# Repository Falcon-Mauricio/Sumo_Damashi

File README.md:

# Sumo DAMASHI

**Damashi** es un robot de sumo autónomo diseñado para competir en la disciplina de **<a href="https://lnr-argentina.com.ar/reglamentos/Reglamento%20Sumo.pdf" target="_blank">Sumo autónomo</a>** organizada por la **<a href="https://lnr-argentina.com.ar/" target="_blank">LNR</a>**.  

<div align="center">
  
</div>

---

## 🚀 Características principales

| Especificación | Detalle |
|----------------|---------|
| **Dimensiones** | 190x190x65 mm |
| **Peso** | ≤ 2500 g |
| **Chasis** | Impreso en 3D |
| **Batería** | LiPo 4S |
| **Microcontrolador** | ESP32 DevKit V1 |
| **Sensores** | 3 x QRE1113GR (tatami) + 5 x SHARP GP2Y0A02YK0F de distancia (laterales y frontales) |
| **Motores** | APYS SP6 - 260 RPM |
| **Driver de motores** | BTS7960 |

---

## ⚡ Entradas / Salidas (I/O)

<table>
<tr>

<td>

### Entradas (sensores y botones)

| Pin ESP32 | Descripción |
|-----------|-------------|
| GPIO34 | SHARP_LEFT |
| GPIO35 | SHARP_RIGHT |
| GPIO32 | SHARP_MID_LEFT |
| GPIO33 | SHARP_MID |
| GPIO25 | SHARP_MID_RIGHT |
| GPIO26 | TATAMI_B (sensor tatami trasero) |
| GPIO27 | TATAMI_L (sensor tatami izquierdo) |
| GPIO13 | TATAMI_R (sensor tatami derecho) |
| GPIO17 | PUSH_2 |
| GPIO18 | PUSH_1 |

</td>

<td>

### Salidas (motores y otros)

| Pin ESP32 | Descripción |
|-----------|-------------|
| GPIO23 | M2B |
| GPIO22 | M2A |
| GPIO19 | M1A |
| GPIO21 | M1B |
| GPIO18 | BUZZER |
| GPIO05 | LED_1 |

</td>

</tr>
</table>

---

## 🛠 Tecnologías utilizadas

- **FreeCAD** → Diseño de piezas 3D (soporte de motores, chasis y demas piezas auxiliares)  
- **KiCad** → Diseño del PCB  
- **PlatformIO (VSCode)** → Firmware en ESP32 (C++ / Arduino framework)  

---

## 📂 Archivos

- `1_hardware_pcb/` → Archivos de KiCad (PCB + esquemas)  
- `2_hardware_chasis/` → Archivos Free

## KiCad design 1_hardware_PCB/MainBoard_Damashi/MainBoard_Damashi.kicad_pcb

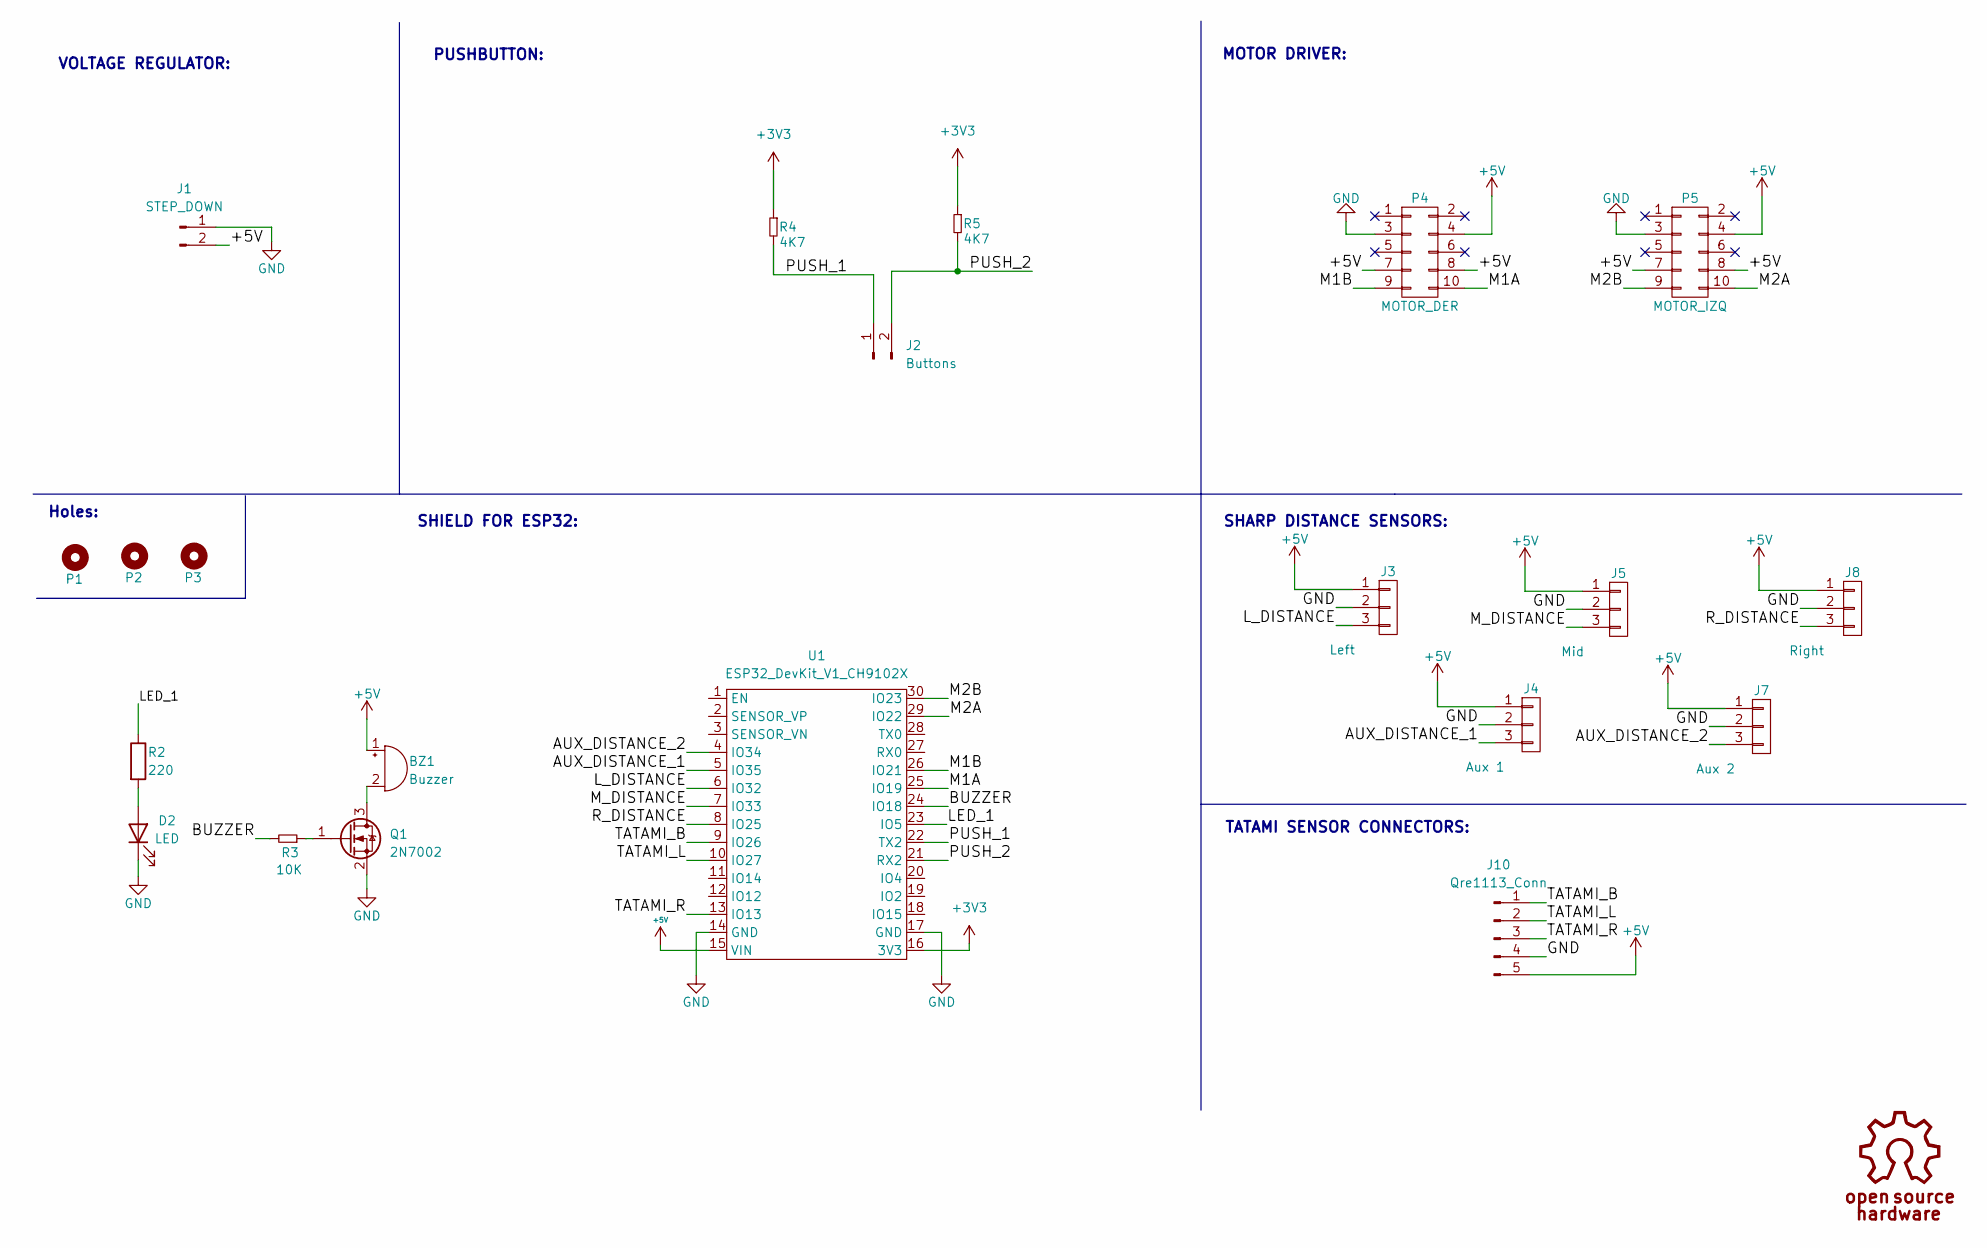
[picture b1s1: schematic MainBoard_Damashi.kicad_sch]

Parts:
BZ1: Buzzer; Buzzer_12mm
D2: LED; PinHeader_1x02_P2.54mm_Horizontal
J1: STEP_DOWN; PinHeader_1x02_P2.54mm_Horizontal
J2: Buttons; PinHeader_1x02_P2.54mm_Horizontal
J3: Left; FanPinHeader_1x03_P2.54mm_Vertical
J4: Aux 1; FanPinHeader_1x03_P2.54mm_Vertical
J5: Mid; FanPinHeader_1x03_P2.54mm_Vertical
J7: Aux 2; FanPinHeader_1x03_P2.54mm_Vertical
J8: Right; FanPinHeader_1x03_P2.54mm_Vertical
J10: Qre1113_Conn; PinHeader_1x05_P2.54mm_Horizontal
P1, P2, P3: Mounting_Hole; Separador_M3_5mm
P4: MOTOR_DER; Header_2x05x2.54mm_Vertical
P5: MOTOR_IZQ; Header_2x05x2.54mm_Vertical
Q1: 2N7002; SOT-23
R2: 220; R_1206
R3: 10K; R_1206
R4, R5: 4K7; R_1206
U1: ESP32_DevKit_V1_CH9102X

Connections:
+3V3: R4.1, R5.1, U1.16 (3V3)
+5V: BZ1.1 (-), J1.2, J3.1, J4.1, J5.1, J7.1, J8.1, J10.5, P4.4, P4.7, P4.8, P5.4, P5.7, P5.8, U1.15 (VIN)
/AUX_DISTANCE_1: J4.3, U1.5 (IO35)
/AUX_DISTANCE_2: J7.3, U1.4 (IO34)
/BUZZER: R3.2, U1.24 (IO18)
/LED_1: R2.1, U1.23 (IO5)
/L_DISTANCE: J3.3, U1.6 (IO32)
/M1A: P4.10, U1.25 (IO19)
/M1B: P4.9, U1.26 (IO21)
/M2A: P5.10, U1.29 (IO22)
/M2B: P5.9, U1.30 (IO23)
/M_DISTANCE: J5.3, U1.7 (IO33)
/PUSH_1: J2.1, R4.2, U1.22 (TX2)
/PUSH_2: J2.2, R5.2, U1.21 (RX2)
/R_DISTANCE: J8.3, U1.8 (IO25)
/TATAMI_B: J10.1, U1.9 (IO26)
/TATAMI_L: J10.2, U1.10 (IO27)
/TATAMI_R: J10.3, U1.13 (IO13)
GND: D2.1 (K), J1.1, J3.2, J4.2, J5.2, J7.2, J8.2, J10.4, P4.3, P5.3, Q1.2 (S), U1.14 (GND), U1.17 (GND)
unnamed: BZ1.2 (+), Q1.3 (D)
unnamed: D2.2 (A), R2.2
unnamed: Q1.1 (G), R3.1

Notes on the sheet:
TATAMI SENSOR CONNECTORS:
SHARP DISTANCE SENSORS:
MOTOR DRIVER:
VOLTAGE REGULATOR:
Holes:
PUSHBUTTON:
SHIELD FOR ESP32:

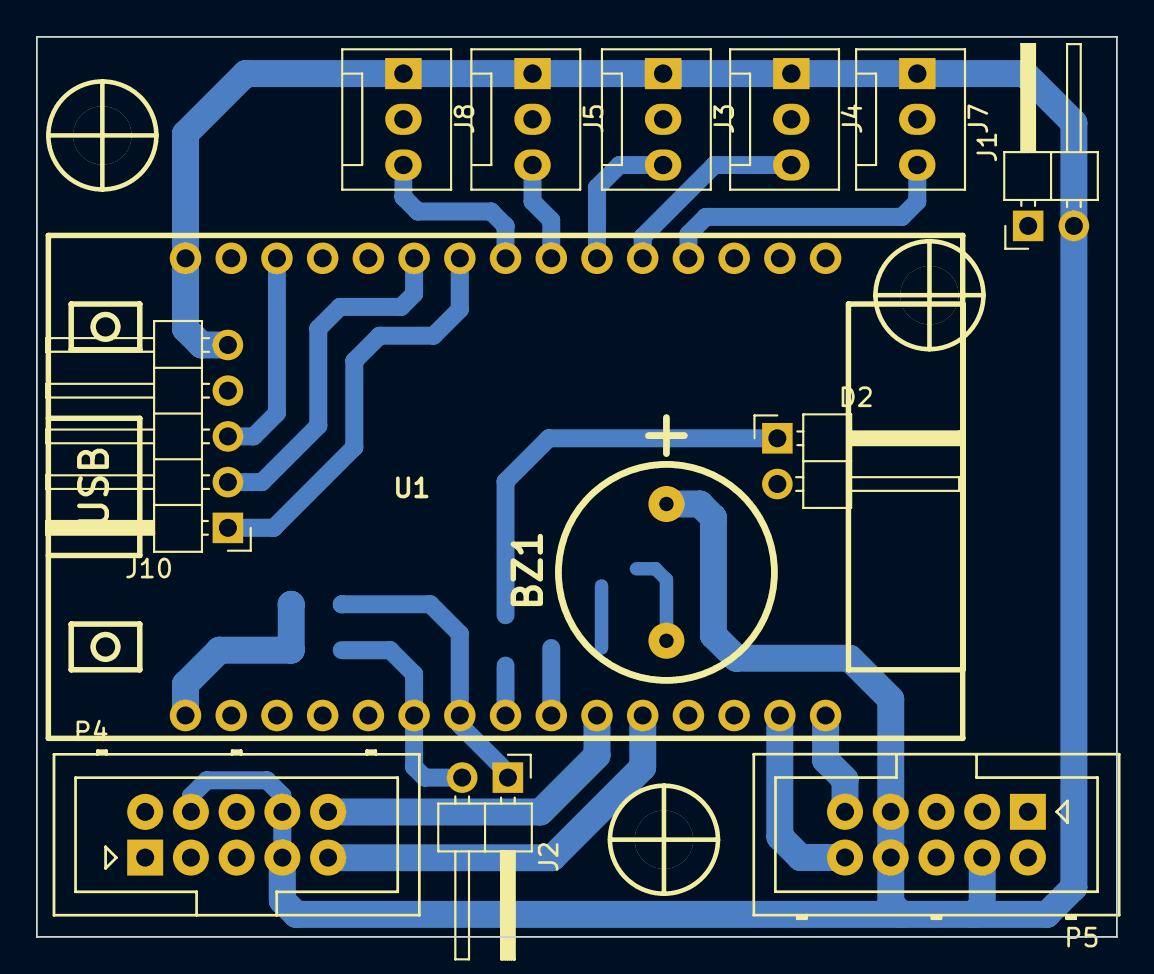
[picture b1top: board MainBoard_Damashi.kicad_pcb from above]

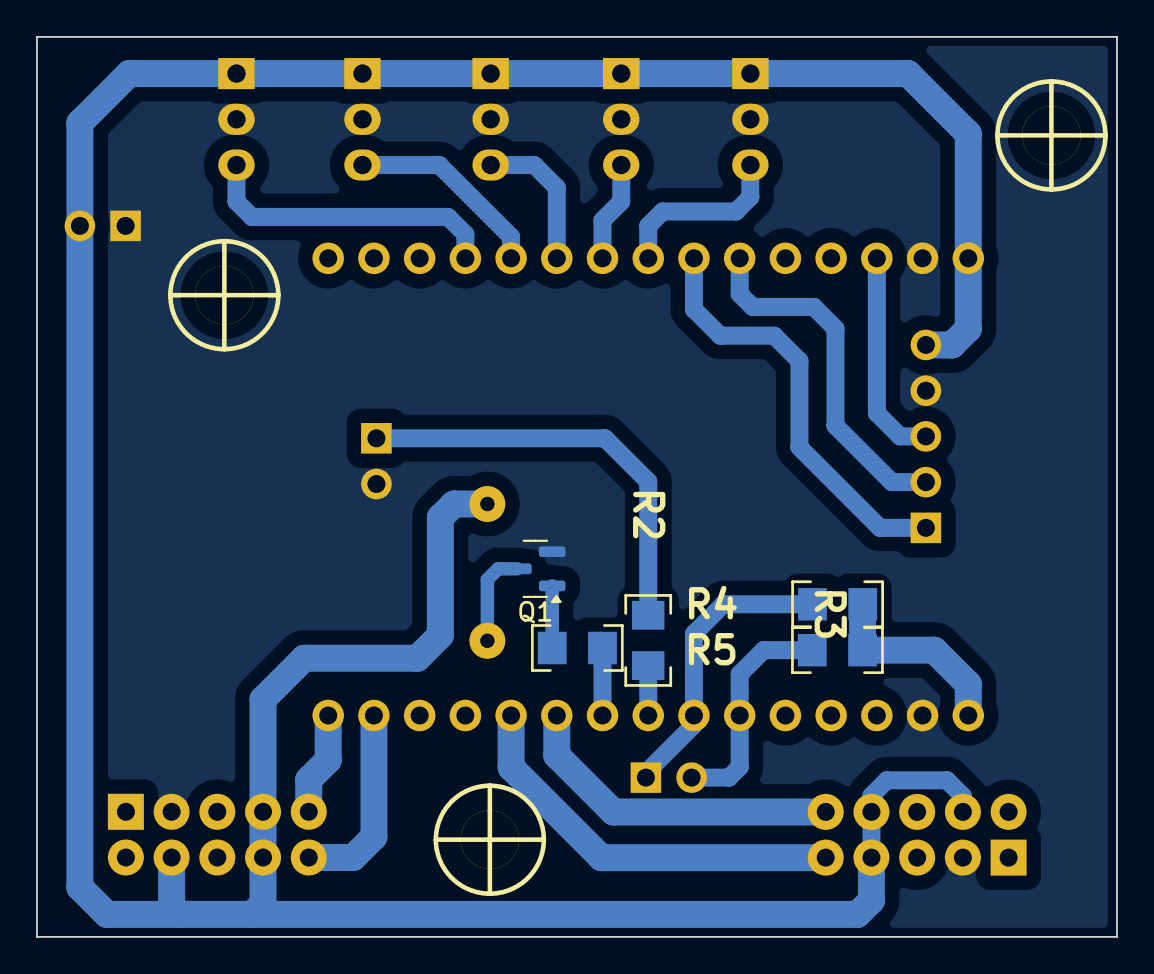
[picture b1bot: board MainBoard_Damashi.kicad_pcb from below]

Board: 2 copper layers, 60.0 x 50.0 mm, 21 parts (5 on the bottom side), 22 nets.

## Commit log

2025-08-25 Diseñe el SCH
2025-08-26 Diseñe el PCB
2025-08-27 Diseñe el Chasis
2025-08-27 Terminado el modelado 3D por completo
